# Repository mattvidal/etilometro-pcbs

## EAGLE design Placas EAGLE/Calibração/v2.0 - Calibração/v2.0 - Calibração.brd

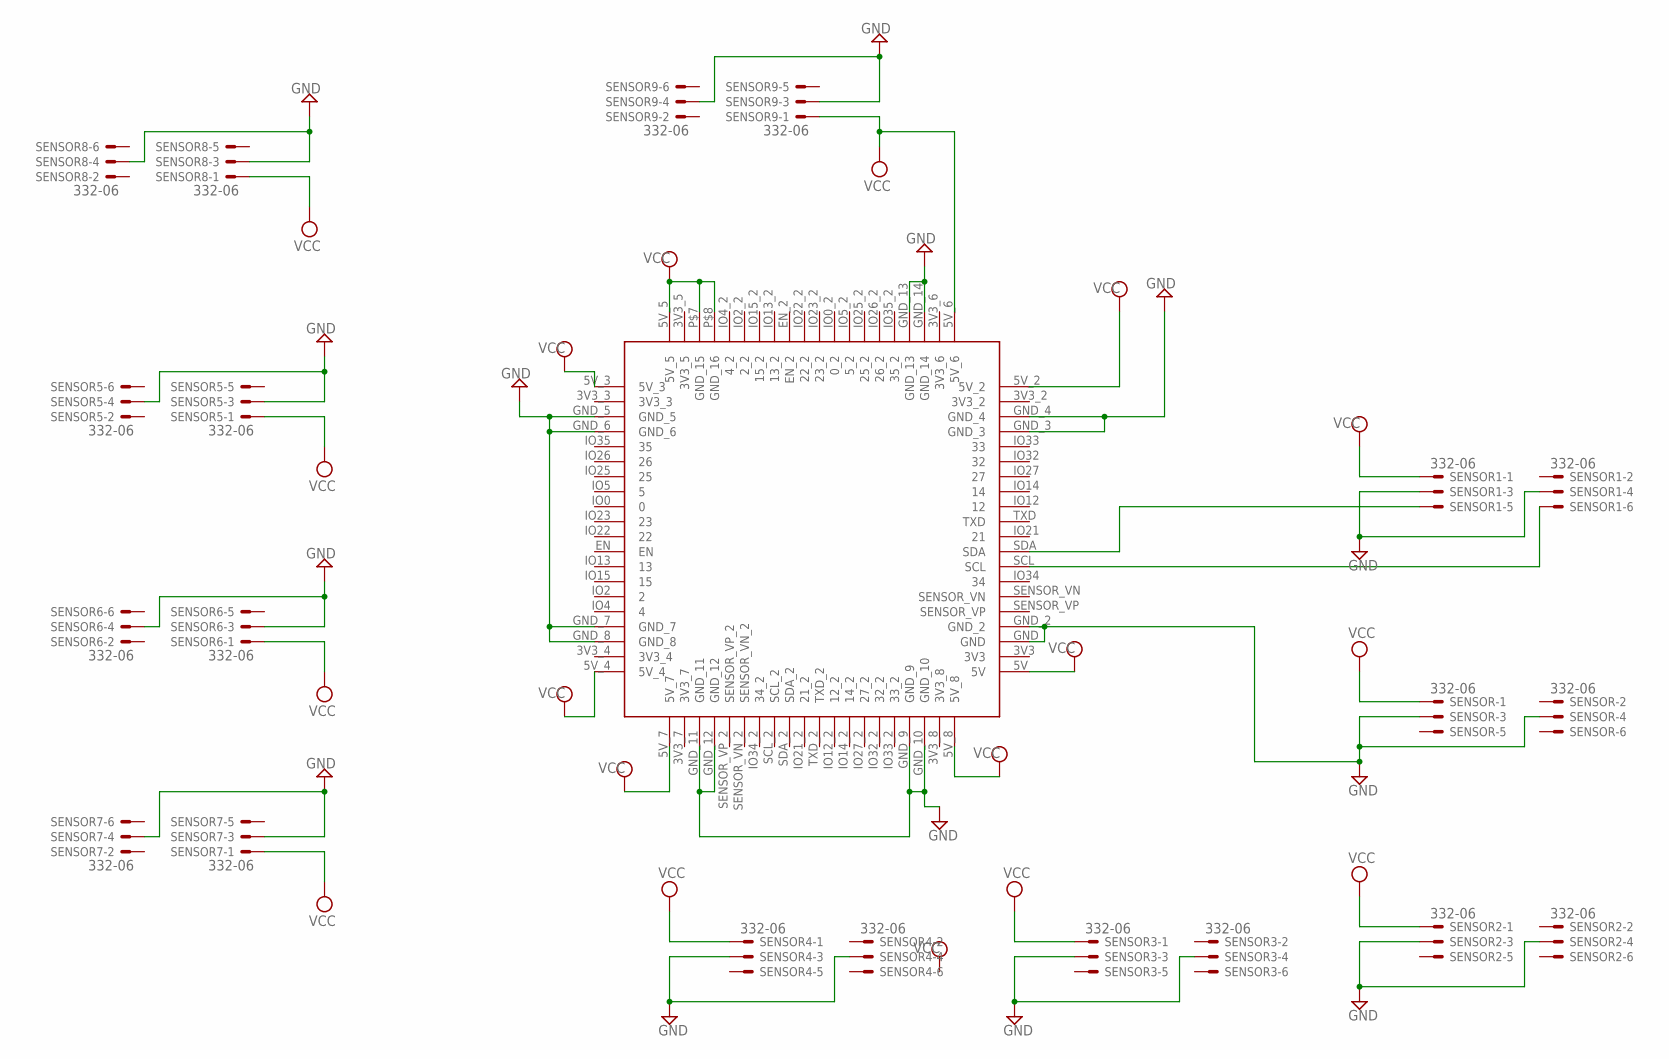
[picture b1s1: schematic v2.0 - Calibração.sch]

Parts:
SENSOR, SENSOR1, SENSOR2, SENSOR3, SENSOR4, SENSOR5, SENSOR6, SENSOR7, SENSOR8, SENSOR9: 332-06
U$1: WT32_SC01; WT32

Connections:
GND: SENSOR.3, SENSOR.4, SENSOR1.3, SENSOR1.4, SENSOR2.3, SENSOR2.4, SENSOR3.3, SENSOR3.4, SENSOR4.3, SENSOR4.4, SENSOR5.3, SENSOR5.4, SENSOR6.3, SENSOR6.4, SENSOR7.3, SENSOR7.4, SENSOR8.3, SENSOR8.4, SENSOR9.3, SENSOR9.4, U$1.GND, U$1.GND_2, U$1.GND_3, U$1.GND_4, U$1.GND_5, U$1.GND_6, U$1.GND_7, U$1.GND_8, U$1.GND_9, U$1.GND_10, U$1.GND_11, U$1.GND_12, U$1.GND_13, U$1.GND_14
unnamed: SENSOR1.5, U$1.SDA
unnamed: SENSOR1.6, U$1.SCL
VCC: SENSOR.1, SENSOR1.1, SENSOR2.1, SENSOR3.1, SENSOR4.1, SENSOR5.1, SENSOR6.1, SENSOR7.1, SENSOR8.1, SENSOR9.1, U$1.5V, U$1.5V_2, U$1.5V_3, U$1.5V_4, U$1.5V_5, U$1.5V_6, U$1.5V_7, U$1.5V_8, U$1.P$7 (GND_15), U$1.P$8 (GND_16)

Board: 2 copper layers, 11 parts (5 on the bottom side), 4 nets, no tracks yet.

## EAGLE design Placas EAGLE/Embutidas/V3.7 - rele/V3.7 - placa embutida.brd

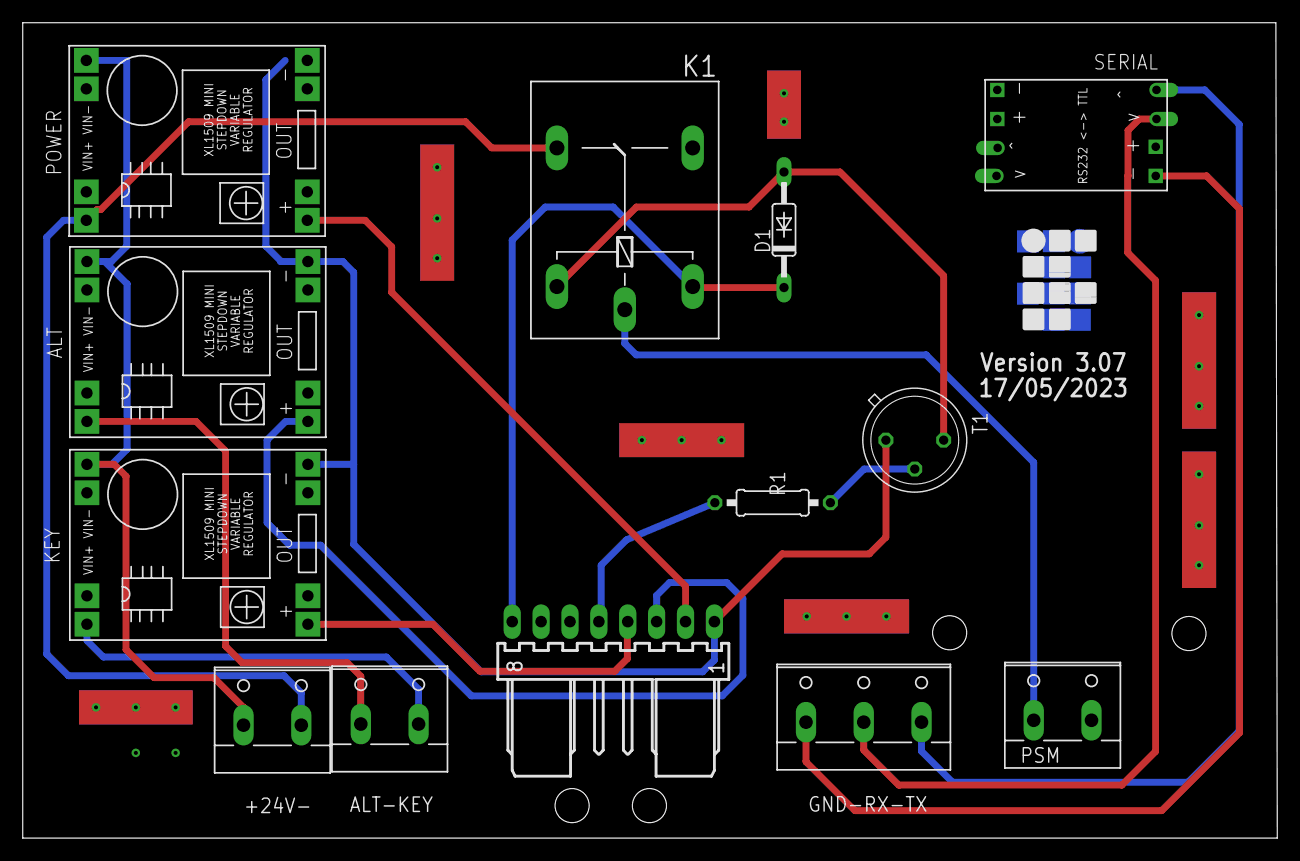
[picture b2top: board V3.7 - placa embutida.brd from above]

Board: 2 copper layers, 110.3 x 71.7 mm, 13 parts (0 on the bottom side), 18 nets.

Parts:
+24V-: +24V-; W237-132
ALT: XL1509WITH_SMDPADS&THROUGHHOLES; XL1509
ALT-KEY: Alt Key; W237-132
D1: 1N4446; DO35-10
GND-RX-TX: RS232; W237-133
J1: Espiral; 7395-08
K1: G5LE
KEY: XL1509WITH_SMDPADS&THROUGHHOLES; XL1509
POWER: XL1509WITH_SMDPADS&THROUGHHOLES; XL1509
PSM: PSM; W237-132
R1: 0207/10
SERIAL: MAX3232WITH_SMDPADS&THROUGHHOLES; MAX3232
T1: 2N2102; TO5

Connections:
CHAVE: ALT.1, J1.3
GRD: ALT.2, J1.1, KEY.2, POWER.2, SERIAL.1, T1.1
unnamed: +24V-.1, ALT.4, KEY.4, POWER.4
unnamed: +24V-.2, K1.O, POWER.3
unnamed: J1.2, POWER.1, SERIAL.2
unnamed: GND-RX-TX.1, SERIAL.8
unnamed: ALT.3, ALT-KEY.1
unnamed: ALT-KEY.2, KEY.3
unnamed: GND-RX-TX.2, SERIAL.6
unnamed: GND-RX-TX.3, SERIAL.5
unnamed: J1.5, R1.2
unnamed: R1.1, T1.2
unnamed: J1.4, KEY.1
unnamed: D1.A, K1.2, T1.3
unnamed: D1.C, J1.8, K1.1
unnamed: K1.P, PSM.1
RX: J1.6, SERIAL.4
TX: J1.7, SERIAL.3

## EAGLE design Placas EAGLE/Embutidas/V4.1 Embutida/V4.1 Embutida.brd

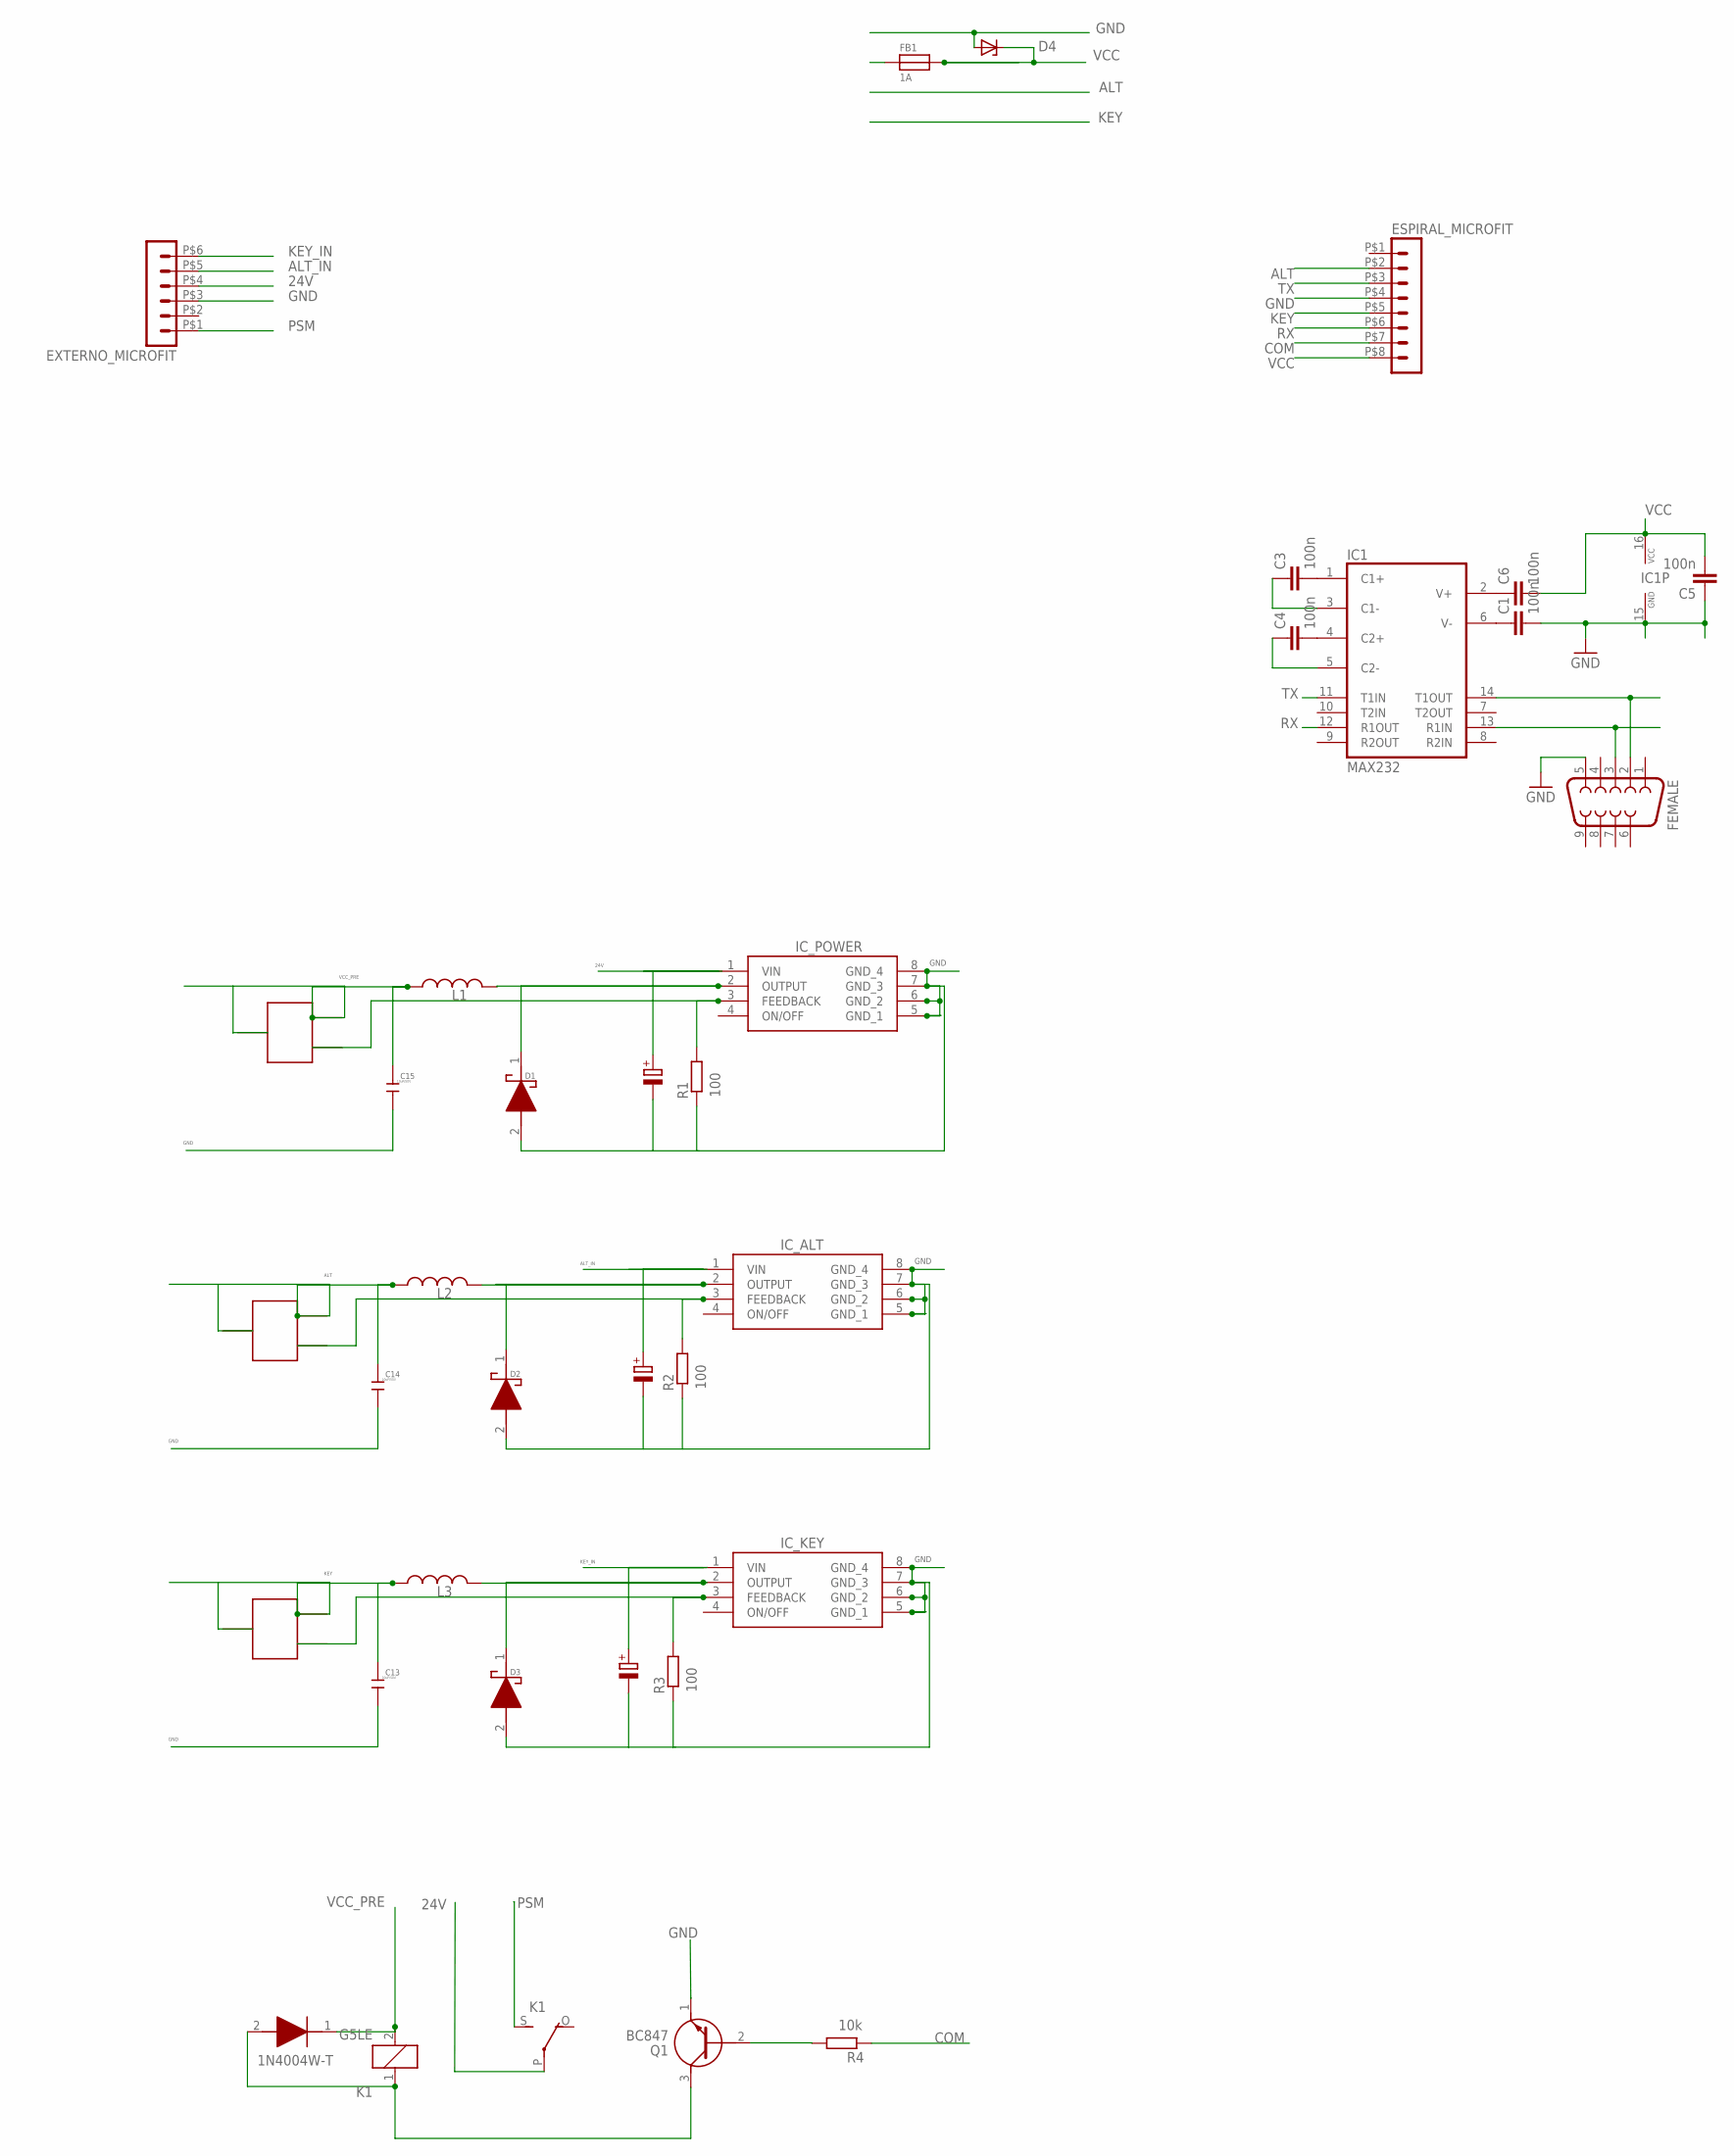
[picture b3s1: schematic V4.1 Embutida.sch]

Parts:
C1, C3, C4, C5, C6: 100n; C0805; MPN C0805C104K8RACAUTO
C2: 22uF/50v; PANASONIC_D; MPN EEH-ZA1H220P
C8, C9: 22uF/50V; PANASONIC_D; MPN EEH-ZA1H220P
C13, C14, C15: 10uF/50V; C0805; MPN C2012X5R1H106K125AC
D1, D2, D3: 1N5819HW1-7-F; SODFL3518X115N; MPN 1N5822 SS34
D4: ZENER-DIODE-SOD123; SOD123FL
D5: 1N4004W-T; SODFL3818X130N
ESPIRAL_MICROFIT: HEADER_POS8_43045-0800; 43045-0800; MPN 43045-0800
EXTERNO_MICROFIT: HEADER_POS6_43045-0600; 43045-0600; MPN 43045-0600
FB1: 1A; 0805; MPN BLM21AG121SN1D
FEMALE: F09H; MPN FEMALE DR9
IC1: MAX232; SO16; MPN MAX3232CSE+
IC_ALT: XL1509-3.3E1; SOIC127P600X175-8N; MPN XL1509-ADJE1
IC_KEY: XL1509-3.3E1; SOIC127P600X175-8N; MPN XL1509-ADJE1
IC_POWER: XL1509-3.3E1; SOIC127P600X175-8N; MPN XL1509-ADJE1
K1: G5LE
L1, L2, L3: 47uH; SDE0604A-470M; MPN SDE0604A-470M
Q1: BC847
R1, R2, R3: 100; R0805; MPN RA73F2A100RBTDF
R4: 10k; R0805; MPN RA73F2A100RBTDF
T1, T2, T3: TRIMPOT 10K; TRIMPOT; MPN EVM3ESX50B14

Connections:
24V: C2.+, EXTERNO_MICROFIT.P$4 (4), IC_POWER.1 (VIN), K1.P
ALT: C14.2, ESPIRAL_MICROFIT.P$2 (2), L2.1, T2.VCC1, T2.VCC2
ALT_IN: C8.+, EXTERNO_MICROFIT.P$5 (5), IC_ALT.1 (VIN)
COM: ESPIRAL_MICROFIT.P$7 (7), R4.1
GND: C1.2, C2.-, C5.1, C8.-, C9.-, C13.1, C14.1, C15.1, D1.2 (A), D2.2 (A), D3.2 (A), D4.A, ESPIRAL_MICROFIT.P$4 (4), EXTERNO_MICROFIT.P$3 (3), FEMALE.5, IC1.15 (GND), IC_ALT.5 (GND_1), IC_ALT.6 (GND_2), IC_ALT.7 (GND_3), IC_ALT.8 (GND_4), IC_KEY.5 (GND_1), IC_KEY.6 (GND_2), IC_KEY.7 (GND_3), IC_KEY.8 (GND_4), IC_POWER.5 (GND_1), IC_POWER.6 (GND_2), IC_POWER.7 (GND_3), IC_POWER.8 (GND_4), Q1.1 (E), R1.1, R2.1, R3.1
KEY: C13.2, ESPIRAL_MICROFIT.P$5 (5), L3.1, T3.VCC1, T3.VCC2
KEY_IN: C9.+, EXTERNO_MICROFIT.P$6 (6), IC_KEY.1 (VIN)
unnamed: D1.1 (K), IC_POWER.2 (OUTPUT), L1.2
unnamed: D2.1 (K), IC_ALT.2 (OUTPUT), L2.2
unnamed: IC_ALT.3 (FEEDBACK), R2.2, T2.OUT
unnamed: D3.1 (K), IC_KEY.2 (OUTPUT), L3.2
unnamed: IC_KEY.3 (FEEDBACK), R3.2, T3.OUT
unnamed: D5.2 (A), K1.1, Q1.3 (C)
unnamed: IC_POWER.3 (FEEDBACK), R1.2, T1.OUT
unnamed: Q1.2 (B), R4.2
unnamed: C3.2, IC1.1 (C1+)
unnamed: C4.2, IC1.4 (C2+)
unnamed: C3.1, IC1.3 (C1-)
unnamed: C4.1, IC1.5 (C2-)
unnamed: C6.1, IC1.2 (V+)
unnamed: C1.1, IC1.6 (V-)
unnamed: FEMALE.2, IC1.14 (T1OUT)
unnamed: FEMALE.3, IC1.13 (R1IN)
PSM: EXTERNO_MICROFIT.P$1 (1), K1.S
RX: ESPIRAL_MICROFIT.P$6 (6), IC1.12 (R1OUT)
TX: ESPIRAL_MICROFIT.P$3 (3), IC1.11 (T1IN)
VCC: C5.2, C6.2, D4.C, ESPIRAL_MICROFIT.P$8 (8), FB1.2, IC1.16 (VCC)
VCC_PRE: C15.2, D5.1 (K), FB1.1, K1.2, L1.1, T1.VCC1, T1.VCC2

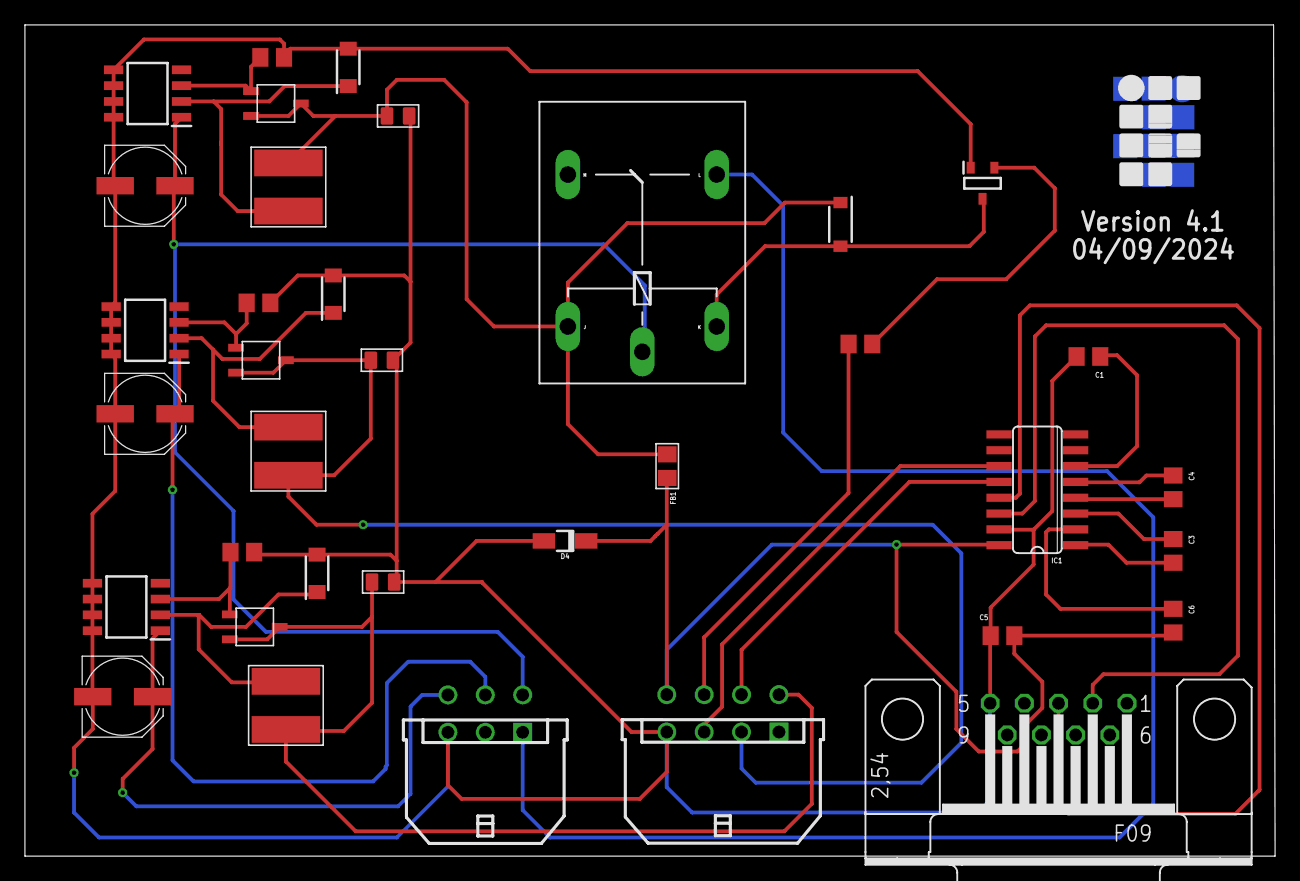
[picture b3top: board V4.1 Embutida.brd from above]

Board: 2 copper layers, 100.3 x 66.7 mm, 36 parts (0 on the bottom side), 28 nets.

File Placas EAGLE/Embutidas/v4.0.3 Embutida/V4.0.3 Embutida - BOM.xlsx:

Part | Value | MPN
C1 | 100n | C0805C104K8RACAUTO
C2 | 22uF/50v | EEH-ZA1H220P
C3 | 100n | C0805C104K8RACAUTO
C4 | 100n | C0805C104K8RACAUTO
C5 | 100n | C0805C104K8RACAUTO
C6 | 100n | C0805C104K8RACAUTO
C8 | 22uF/50V | EEH-ZA1H220P
C9 | 22uF/50V | EEH-ZA1H220P
C10 | 2200 uF | EEV-FK1A222Q
C13 | 10uF/50V | C2012X5R1H106K125AC
C14 | 10uF/50V | C2012X5R1H106K125AC
C15 | 10uF/50V | C2012X5R1H106K125AC
D1 | 1N5819HW1-7-F | 1N5822 SS34
D2 | 1N5819HW1-7-F | 1N5822 SS34
D3 | 1N5819HW1-7-F | 1N5822 SS34
D5 |  | 1N4004W-T
ESPIRAL_MICROFIT |  | 43045-0800
EXTERNO_MICROFIT |  | 43045-0600
FB1 | 1A | BLM21AG121SN1D
FEMALE |  | FEMALE DR9
IC1 | MAX232 | MAX3232CSE+
IC_ALT | XL1509-3.3E1 | XL1509-ADJE1
IC_KEY | XL1509-3.3E1 | XL1509-ADJE1
IC_POWER | XL1509-3.3E1 | XL1509-ADJE1
K1 |  | G5LE
L1 | 47uH | SDE0604A-470M
L2 | 47uH | SDE0604A-470M
L3 | 47uH | SDE0604A-470M
Q1 |  | BC847
R1 | 100 | RA73F2A100RBTDF
R2 | 100 | RA73F2A100RBTDF
R3 | 100 | RA73F2A100RBTDF
R4 | 10k | RA73F2A100RBTDF
T1 | TRIMPOT 10K | EVM3ESX50B14
T2 | TRIMPOT 10K | EVM3ESX50B14
T3 | TRIMPOT 10K | EVM3ESX50B14

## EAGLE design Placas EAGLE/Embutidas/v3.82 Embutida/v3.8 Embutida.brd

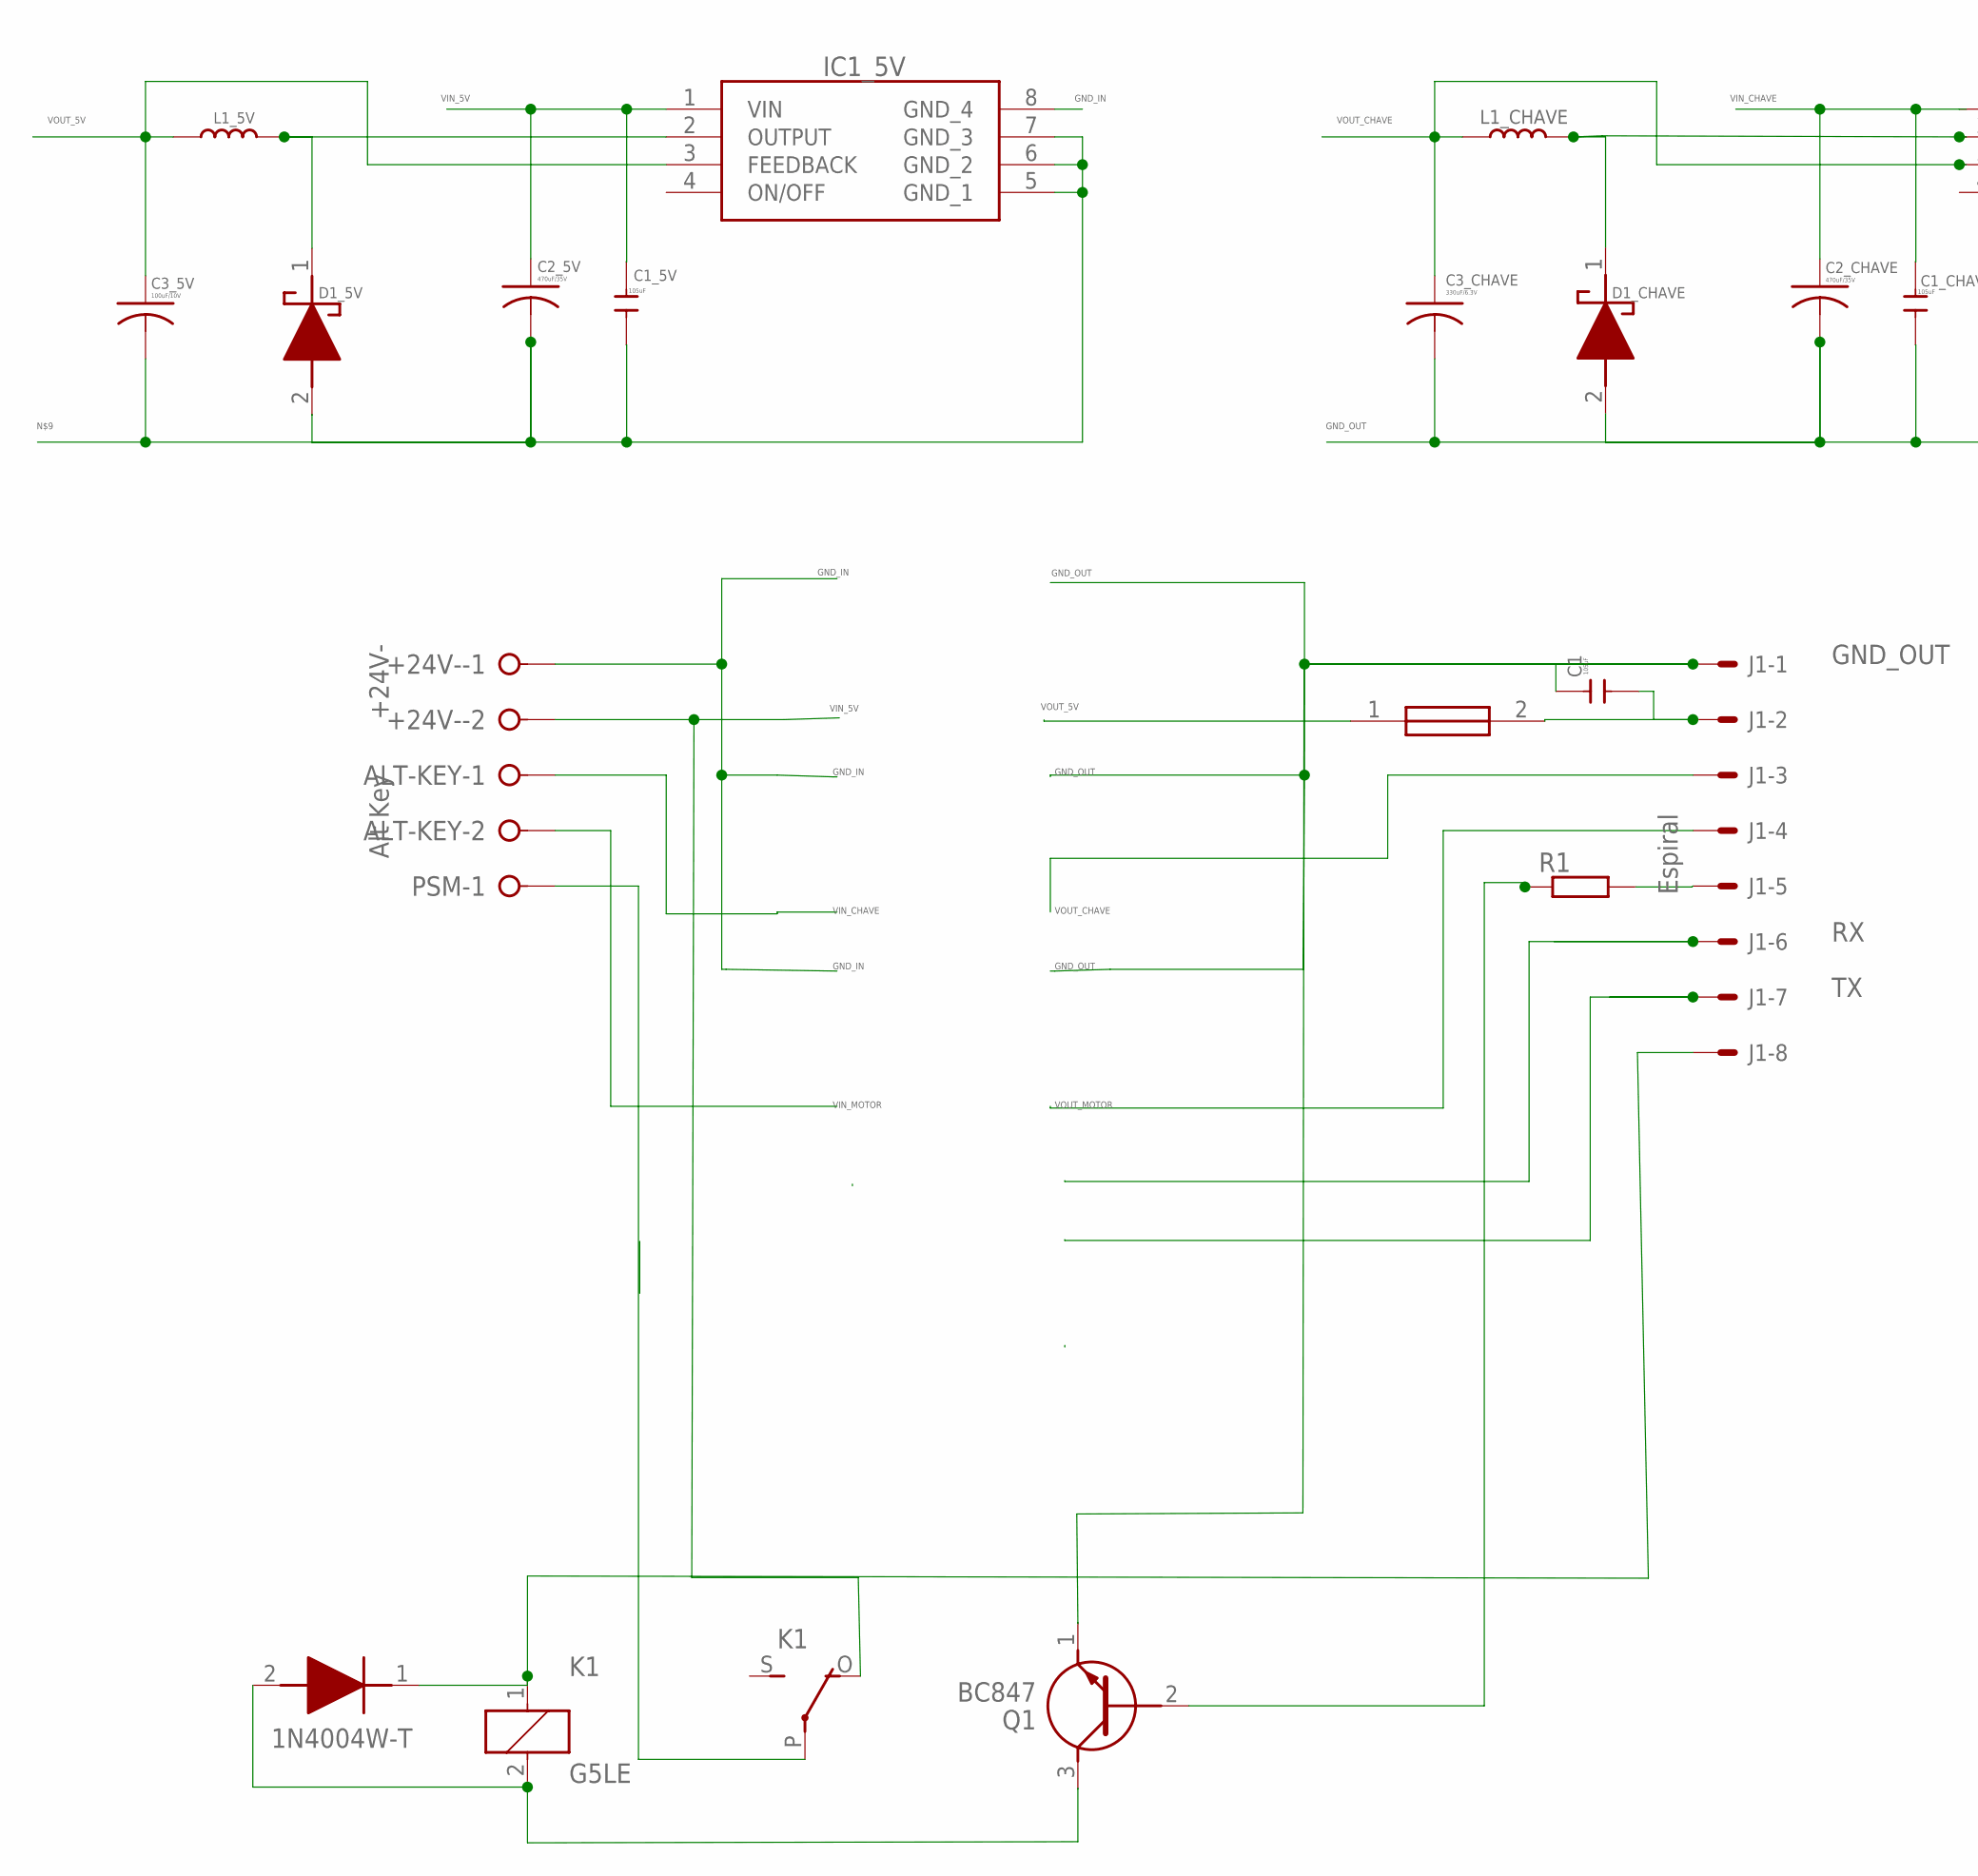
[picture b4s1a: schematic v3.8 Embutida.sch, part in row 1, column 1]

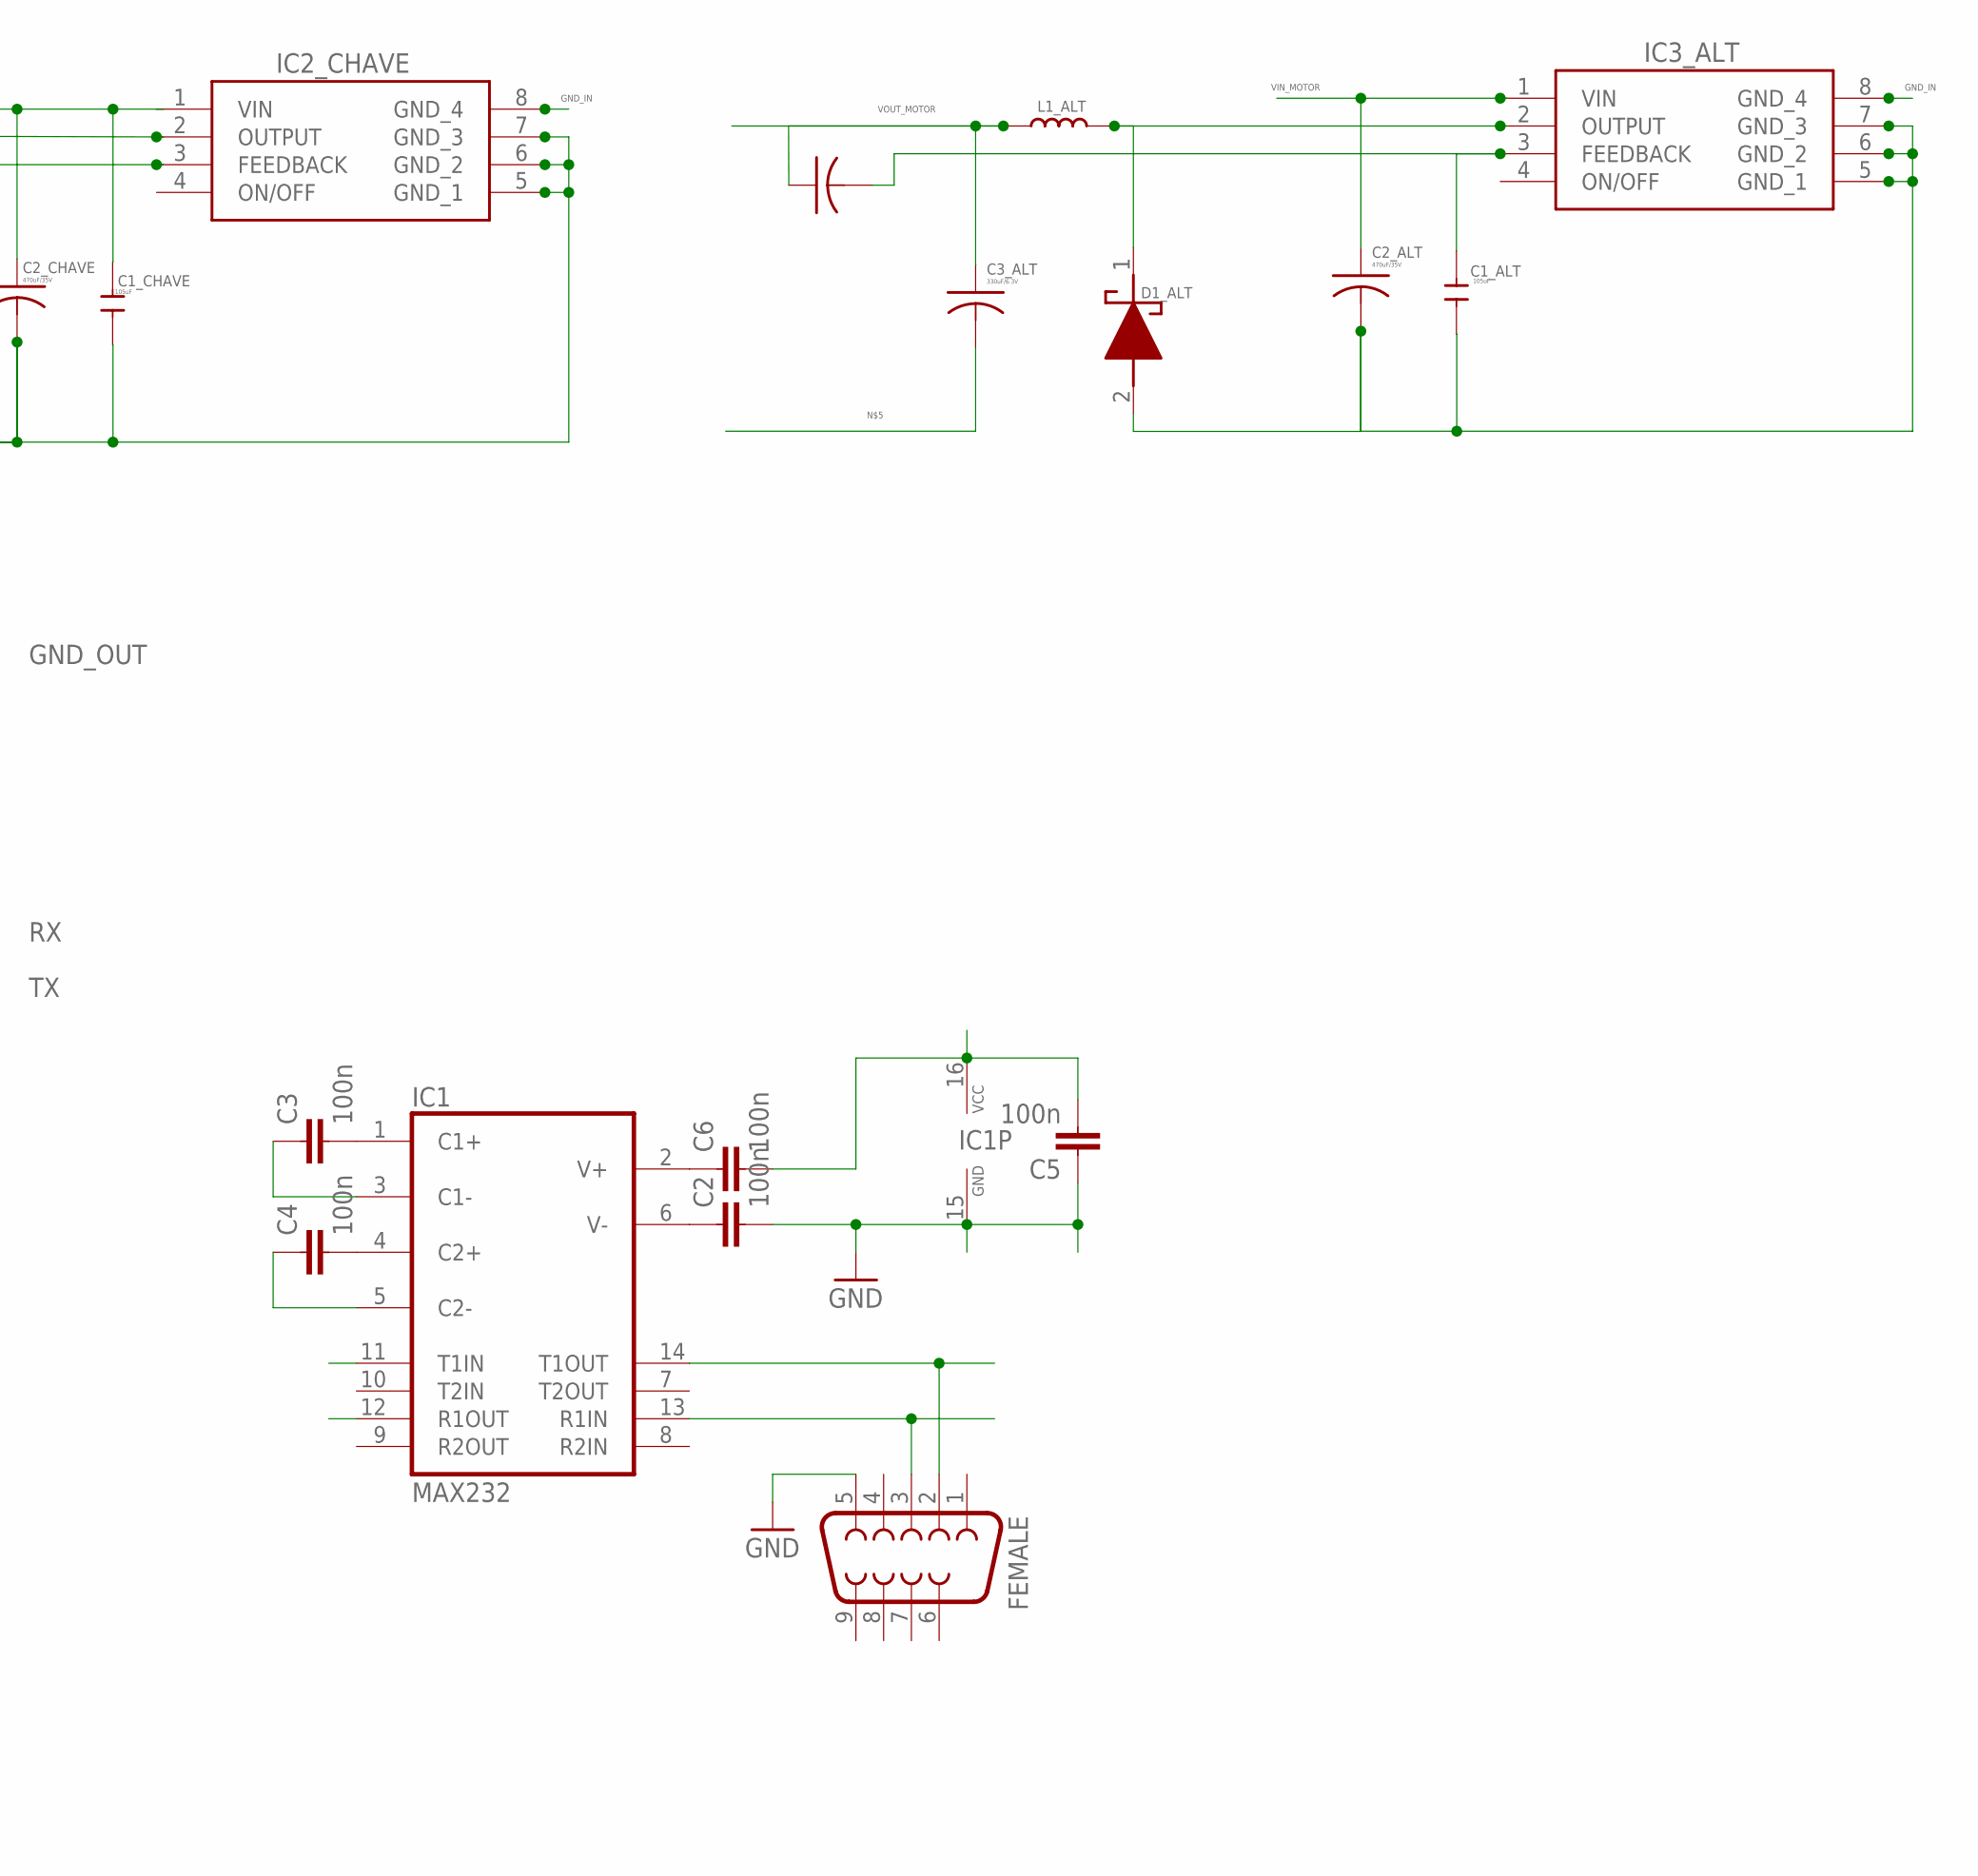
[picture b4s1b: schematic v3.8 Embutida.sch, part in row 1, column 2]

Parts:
+24V-: +24V-; W237-132
ALT-KEY: Alt Key; W237-132
C1, C1_5V, C1_ALT, C1_CHAVE: 105uF; C0805
C2, C3, C4, C5, C6: 100n; C0805
C2_5V, C2_ALT, C2_CHAVE: 470uF/35V; C0201
C3_5V: 100uF/10V; C0201
C3_ALT, C3_ALT1, C3_CHAVE: 330uF/6.3V; C0201
D1_5V, D1_ALT, D1_CHAVE: 1N5819HW1-7-F; SODFL3518X115N
D2: 1N4004W-T; SODFL3818X130N
F2: 0679H1000-05; FUSC6125X279N
FEMALE: F09H
IC1: MAX232; SO16
IC1_5V: XL1509-5.0E1; SOIC127P600X175-8N
IC2_CHAVE, IC3_ALT: XL1509-3.3E1; SOIC127P600X175-8N
J1: Espiral; 7395-08
K1: G5LE
L1_5V: 68uH; PIO73
L1_ALT, L1_CHAVE: 47uH; PIO73
PSM: PSM; W237-132
Q1: BC847
R1: 10k; SMS-WAV

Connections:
5V: C5.2, C6.2, IC1.16 (VCC)
GND: C2.2, C5.1, FEMALE.5, IC1.15 (GND)
GND_IN: +24V-.1, IC1_5V.8 (GND_4), IC2_CHAVE.8 (GND_4), IC3_ALT.8 (GND_4)
GND_OUT: C1.2, C1_ALT.1, C1_CHAVE.1, C2_ALT.2, C2_CHAVE.2, C3_CHAVE.2, D1_ALT.2 (A), D1_CHAVE.2 (A), IC2_CHAVE.5 (GND_1), IC2_CHAVE.6 (GND_2), IC2_CHAVE.7 (GND_3), IC3_ALT.5 (GND_1), IC3_ALT.6 (GND_2), IC3_ALT.7 (GND_3), J1.1, Q1.1 (E)
unnamed: D1_CHAVE.1 (K), IC2_CHAVE.2 (OUTPUT), L1_CHAVE.1
unnamed: D1_5V.1 (K), IC1_5V.2 (OUTPUT), L1_5V.1
unnamed: D1_ALT.1 (K), IC3_ALT.2 (OUTPUT), L1_ALT.1
unnamed: J1.5, R1.1
unnamed: Q1.2 (B), R1.2
unnamed: C1_ALT.2, C3_ALT1.2, IC3_ALT.3 (FEEDBACK)
unnamed: C1_5V.1, C2_5V.2, C3_5V.2, D1_5V.2 (A), IC1_5V.5 (GND_1), IC1_5V.6 (GND_2), IC1_5V.7 (GND_3)
unnamed: C3.2, IC1.1 (C1+)
unnamed: C1.1, F2.2, J1.2
unnamed: C4.2, IC1.4 (C2+)
unnamed: C3.1, IC1.3 (C1-)
unnamed: C4.1, IC1.5 (C2-)
unnamed: C6.1, IC1.2 (V+)
unnamed: C2.1, IC1.6 (V-)
unnamed: FEMALE.2, IC1.14 (T1OUT)
unnamed: FEMALE.3, IC1.13 (R1IN)
unnamed: D2.2 (A), K1.2, Q1.3 (C)
unnamed: D2.1 (K), J1.8, K1.1
unnamed: K1.P, PSM.1
RX: IC1.12 (R1OUT), J1.6
TX: IC1.11 (T1IN), J1.7
VIN_5V: +24V-.2, C1_5V.2, C2_5V.1, IC1_5V.1 (VIN), K1.O
VIN_CHAVE: ALT-KEY.1, C1_CHAVE.2, C2_CHAVE.1, IC2_CHAVE.1 (VIN)
VIN_MOTOR: ALT-KEY.2, C2_ALT.1, IC3_ALT.1 (VIN)
VOUT_5V: C3_5V.1, F2.1, IC1_5V.3 (FEEDBACK), L1_5V.2
VOUT_CHAVE: C3_CHAVE.1, IC2_CHAVE.3 (FEEDBACK), J1.3, L1_CHAVE.2
VOUT_MOTOR: C3_ALT.1, C3_ALT1.1, J1.4, L1_ALT.2

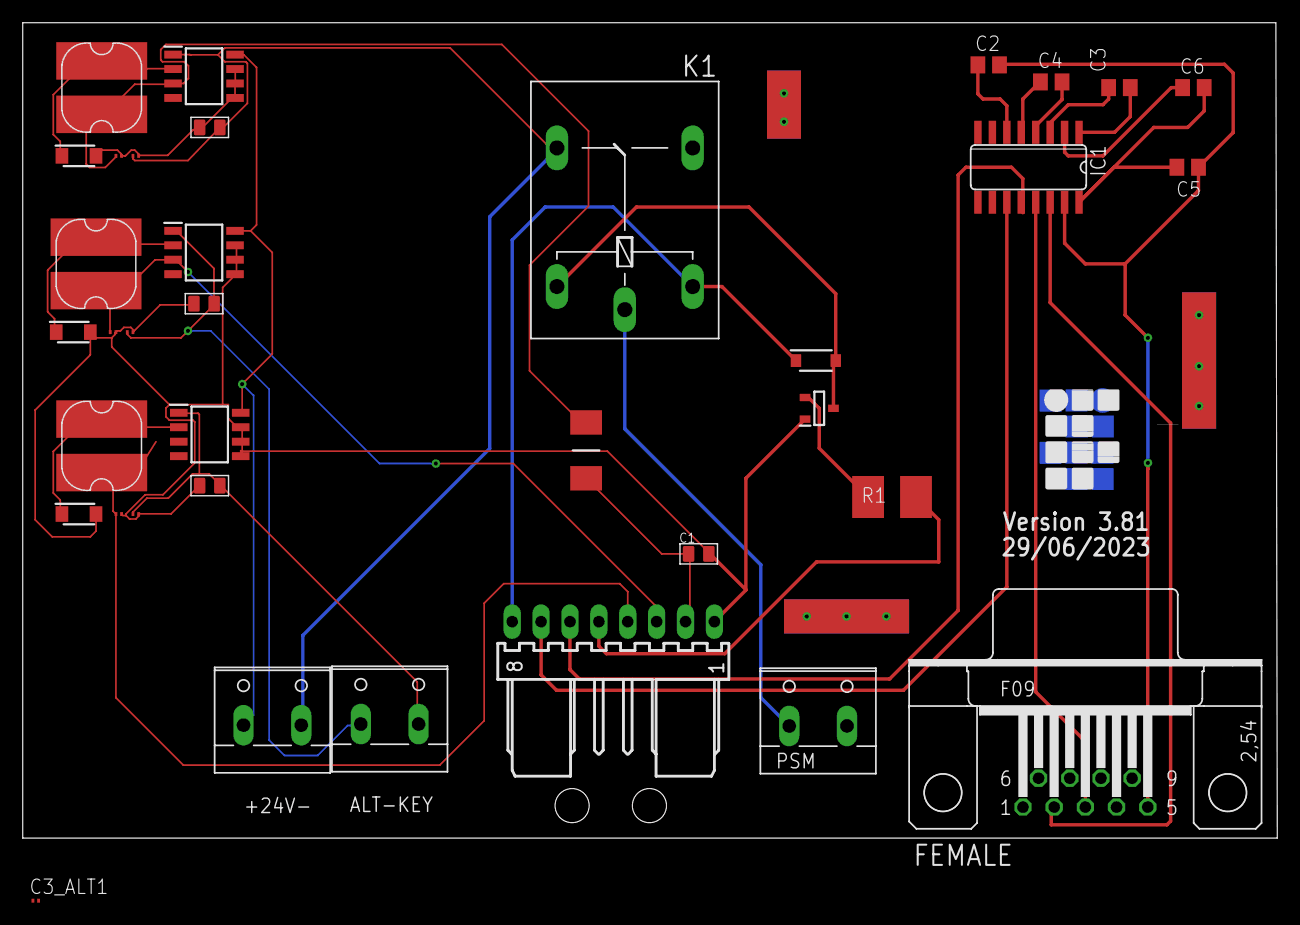
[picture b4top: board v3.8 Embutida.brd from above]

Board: 2 copper layers, 110.3 x 71.7 mm, 36 parts (0 on the bottom side), 31 nets.
